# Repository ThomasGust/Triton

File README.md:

# Triton
Code for the Triton Robotics MATE ROV Competition Team

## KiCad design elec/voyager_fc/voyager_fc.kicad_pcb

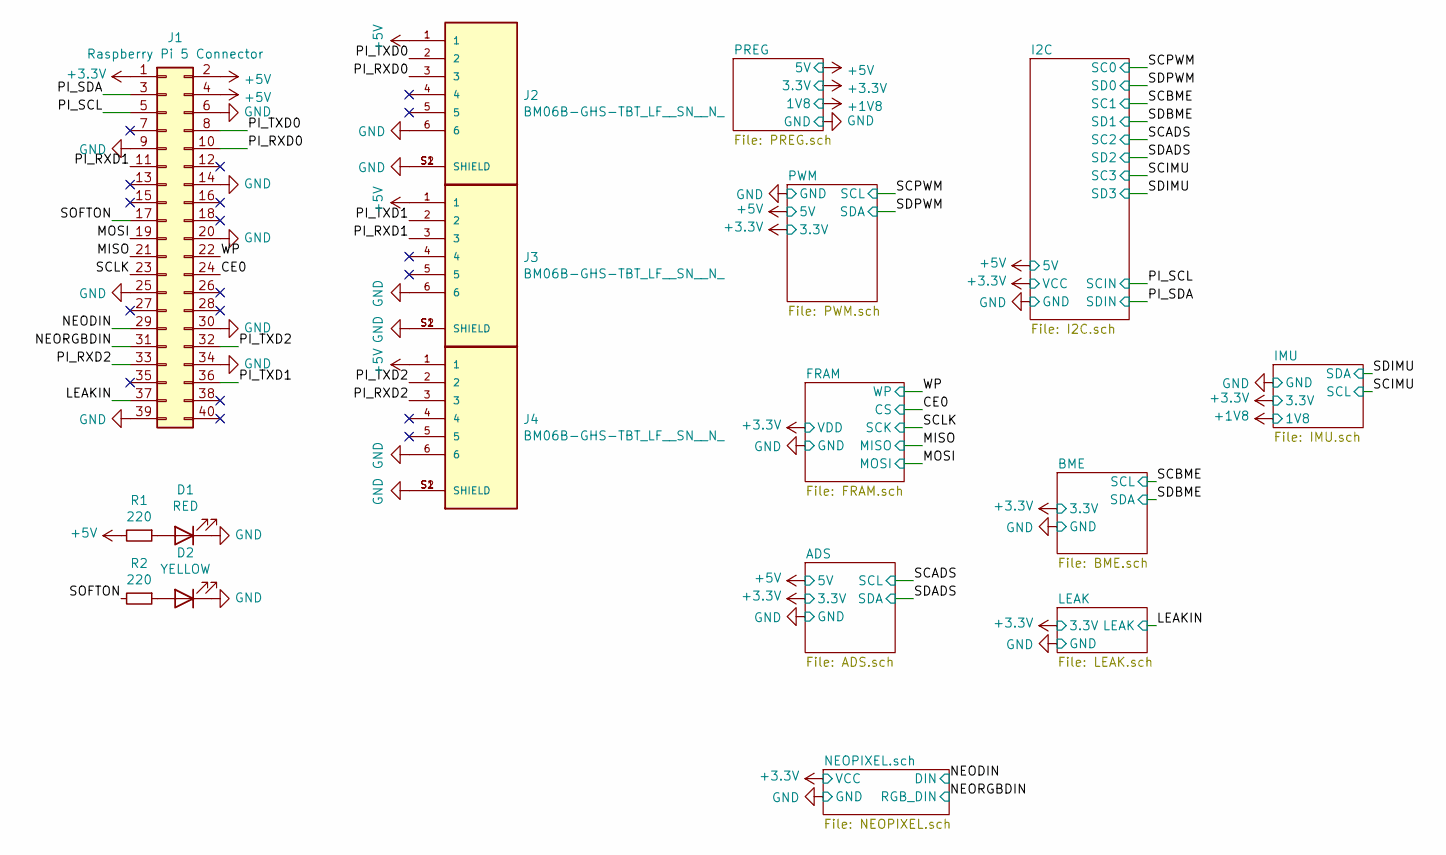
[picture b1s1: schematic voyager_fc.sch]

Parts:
D1: RED; LED_0603_1608Metric
D2: YELLOW; LED_0603_1608Metric
J1: Raspberry Pi 5 Connector; PinSocket_2x20_P2.54mm_Vertical
J2, J3, J4: BM06B-GHS-TBT_LF__SN__N_; JST_BM06B-GHS-TBT_LF__SN__N_; PARTREV N/A
R1, R2: 220; R_0402_1005Metric

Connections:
+3V3: J1.1; also elsewhere on the board
+5V: J1.2, J1.4, J2.1, J3.1, J4.1, R1.2; also elsewhere on the board
/CE0: J1.24; also elsewhere on the board
/LEAKIN: J1.37; also elsewhere on the board
/MISO: J1.21; also elsewhere on the board
/MOSI: J1.19; also elsewhere on the board
/NEODIN: J1.29; also elsewhere on the board
/NEORGBDIN: J1.31; also elsewhere on the board
/PI_RXD0: J1.10, J2.3
/PI_RXD1: J1.11, J3.3
/PI_RXD2: J1.33, J4.3
/PI_SCL: J1.5; also elsewhere on the board
/PI_SDA: J1.3; also elsewhere on the board
/PI_TXD0: J1.8, J2.2
/PI_TXD1: J1.36, J3.2
/PI_TXD2: J1.32, J4.2
/SCLK: J1.23; also elsewhere on the board
/SOFTON: J1.17, R2.2
/WP: J1.22; also elsewhere on the board
GND: D1.1 (K), D2.1 (K), J1.6, J1.9, J1.14, J1.20, J1.25, J1.30, J1.34, J1.39, J2.6, J2.S1 (SHIELD), J2.S2 (SHIELD), J3.6, J3.S1 (SHIELD), J3.S2 (SHIELD), J4.6, J4.S1 (SHIELD), J4.S2 (SHIELD); also elsewhere on the board
unnamed: D1.2 (A), R1.1
unnamed: D2.2 (A), R2.1

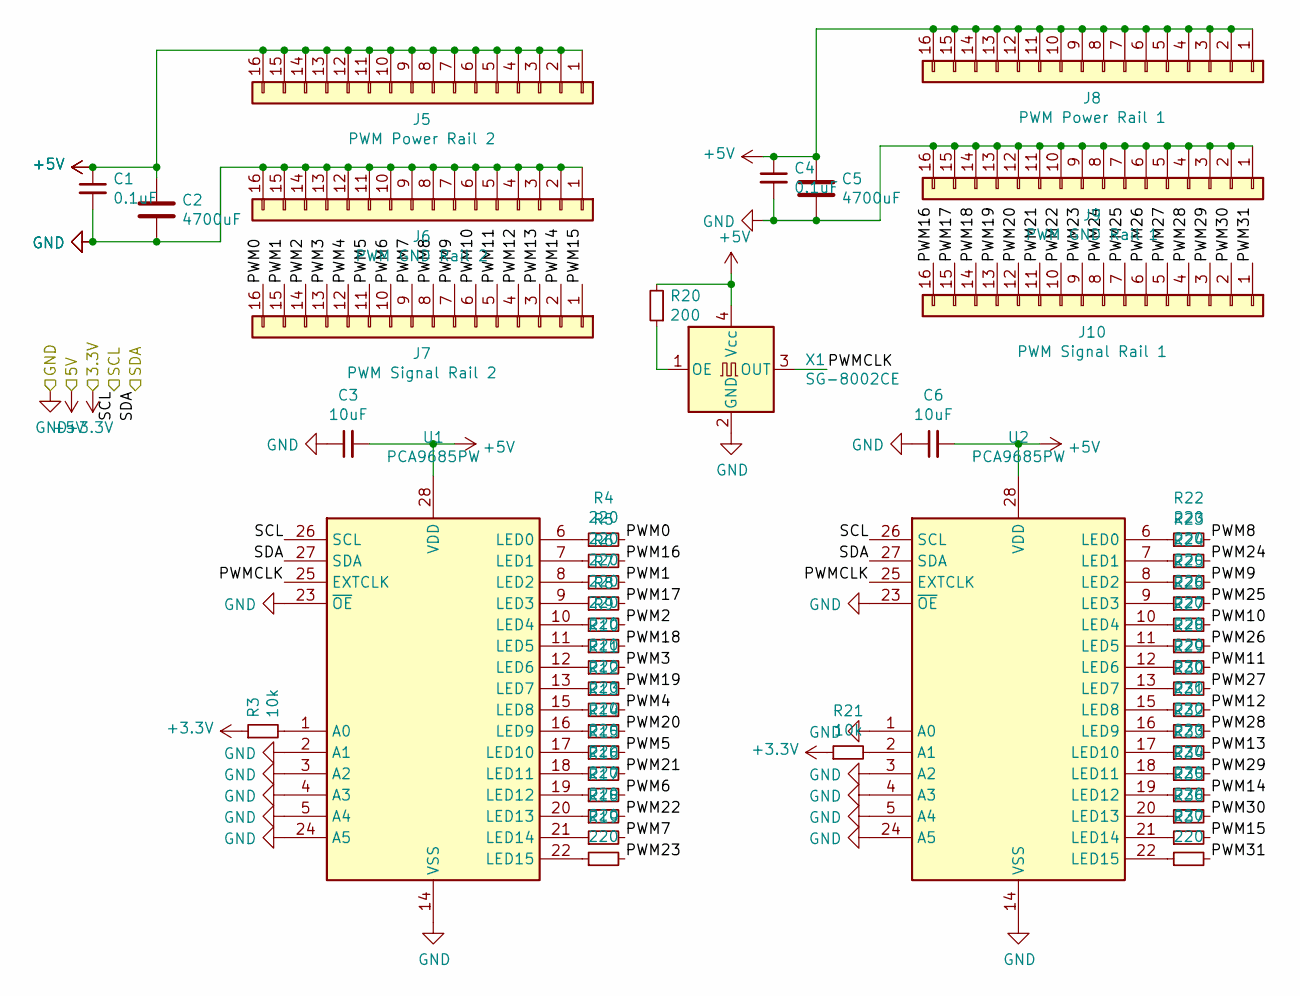
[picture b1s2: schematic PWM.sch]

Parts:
C1, C4: 0.1uF; C_0402_1005Metric
C2, C5: 4700uF; CP_Radial_D10.0mm_P5.00mm
C3, C6: 10uF; C_0603_1608Metric
J5: PWM Power Rail 2; PinHeader_1x16_P2.54mm_Vertical
J6: PWM GND Rail 2; PinHeader_1x16_P2.54mm_Vertical
J7: PWM Signal Rail 2; PinHeader_1x16_P2.54mm_Vertical
J8: PWM Power Rail 1; PinHeader_1x16_P2.54mm_Vertical
J9: PWM GND Rail 1; PinHeader_1x16_P2.54mm_Vertical
J10: PWM Signal Rail 1; PinHeader_1x16_P2.54mm_Vertical
R3, R21: 10k; R_0603_1608Metric
R4, R5, R6, R7, R8, R9, R10, R11, R12, R13, R14, R15, R16, R17, R18, R19, R22, R23, R24, R25, R26, R27, R28, R29, R30, R31, R32, R33, R34, R35, R36, R37: 220; R_0402_1005Metric
R20: 200; R_0402_1005Metric
U1, U2: PCA9685PW; TSSOP-28_4.4x9.7mm_P0.65mm
X1: SG-8002CE; Oscillator_SMD_SeikoEpson_SG8002CE-4Pin_3.2x2.5mm

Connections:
+3V3: R3.1, R21.1; also elsewhere on the board
+5V: C1.1, C2.1, C3.2, C4.1, C5.1, C6.2, J5.1, J5.2, J5.3, J5.4, J5.5, J5.6, J5.7, J5.8, J5.9, J5.10, J5.11, J5.12, J5.13, J5.14, J5.15, J5.16, J8.1, J8.2, J8.3, J8.4, J8.5, J8.6, J8.7, J8.8, J8.9, J8.10, J8.11, J8.12, J8.13, J8.14, J8.15, J8.16, R20.2, U1.28 (VDD), U2.28 (VDD), X1.4 (Vcc); also elsewhere on the board
/PWM/PWM0: J7.16, R4.2
/PWM/PWM1: J7.15, R6.2
/PWM/PWM2: J7.14, R8.2
/PWM/PWM3: J7.13, R10.2
/PWM/PWM4: J7.12, R12.2
/PWM/PWM5: J7.11, R14.2
/PWM/PWM6: J7.10, R16.2
/PWM/PWM7: J7.9, R18.2
/PWM/PWM8: J7.8, R22.2
/PWM/PWM9: J7.7, R24.2
/PWM/PWM10: J7.6, R26.2
/PWM/PWM11: J7.5, R28.2
/PWM/PWM12: J7.4, R30.2
/PWM/PWM13: J7.3, R32.2
/PWM/PWM14: J7.2, R34.2
/PWM/PWM15: J7.1, R36.2
/PWM/PWM16: J10.16, R5.2
/PWM/PWM17: J10.15, R7.2
/PWM/PWM18: J10.14, R9.2
/PWM/PWM19: J10.13, R11.2
/PWM/PWM20: J10.12, R13.2
/PWM/PWM21: J10.11, R15.2
/PWM/PWM22: J10.10, R17.2
/PWM/PWM23: J10.9, R19.2
/PWM/PWM24: J10.8, R23.2
/PWM/PWM25: J10.7, R25.2
/PWM/PWM26: J10.6, R27.2
/PWM/PWM27: J10.5, R29.2
/PWM/PWM28: J10.4, R31.2
/PWM/PWM29: J10.3, R33.2
/PWM/PWM30: J10.2, R35.2
/PWM/PWM31: J10.1, R37.2
/PWM/PWMCLK: U1.25 (EXTCLK), U2.25 (EXTCLK), X1.3 (OUT)
/SCPWM: U1.26 (SCL), U2.26 (SCL); also elsewhere on the board
/SDPWM: U1.27 (SDA), U2.27 (SDA); also elsewhere on the board
GND: C1.2, C2.2, C3.1, C4.2, C5.2, C6.1, J6.1, J6.2, J6.3, J6.4, J6.5, J6.6, J6.7, J6.8, J6.9, J6.10, J6.11, J6.12, J6.13, J6.14, J6.15, J6.16, J9.1, J9.2, J9.3, J9.4, J9.5, J9.6, J9.7, J9.8, J9.9, J9.10, J9.11, J9.12, J9.13, J9.14, J9.15, J9.16, U1.2 (A1), U1.3 (A2), U1.4 (A3), U1.5 (A4), U1.14 (VSS), U1.23 (~OE), U1.24 (A5), U2.1 (A0), U2.3 (A2), U2.4 (A3), U2.5 (A4), U2.14 (VSS), U2.23 (~OE), U2.24 (A5), X1.2 (GND); also elsewhere on the board
unnamed: R3.2, U1.1 (A0)
unnamed: R4.1, U1.6 (LED0)
unnamed: R5.1, U1.7 (LED1)
unnamed: R6.1, U1.8 (LED2)
unnamed: R7.1, U1.9 (LED3)
unnamed: R8.1, U1.10 (LED4)
unnamed: R9.1, U1.11 (LED5)
unnamed: R10.1, U1.12 (LED6)
unnamed: R11.1, U1.13 (LED7)
unnamed: R12.1, U1.15 (LED8)
unnamed: R13.1, U1.16 (LED9)
unnamed: R14.1, U1.17 (LED10)
unnamed: R15.1, U1.18 (LED11)
unnamed: R16.1, U1.19 (LED12)
unnamed: R17.1, U1.20 (LED13)
unnamed: R18.1, U1.21 (LED14)
unnamed: R19.1, U1.22 (LED15)
unnamed: R20.1, X1.1 (OE)
unnamed: R21.2, U2.2 (A1)
unnamed: R22.1, U2.6 (LED0)
unnamed: R23.1, U2.7 (LED1)
unnamed: R24.1, U2.8 (LED2)
unnamed: R25.1, U2.9 (LED3)
unnamed: R26.1, U2.10 (LED4)
unnamed: R27.1, U2.11 (LED5)
unnamed: R28.1, U2.12 (LED6)
unnamed: R29.1, U2.13 (LED7)
unnamed: R30.1, U2.15 (LED8)
unnamed: R31.1, U2.16 (LED9)
unnamed: R32.1, U2.17 (LED10)
unnamed: R33.1, U2.18 (LED11)
unnamed: R34.1, U2.19 (LED12)
unnamed: R35.1, U2.20 (LED13)
unnamed: R36.1, U2.21 (LED14)
unnamed: R37.1, U2.22 (LED15)

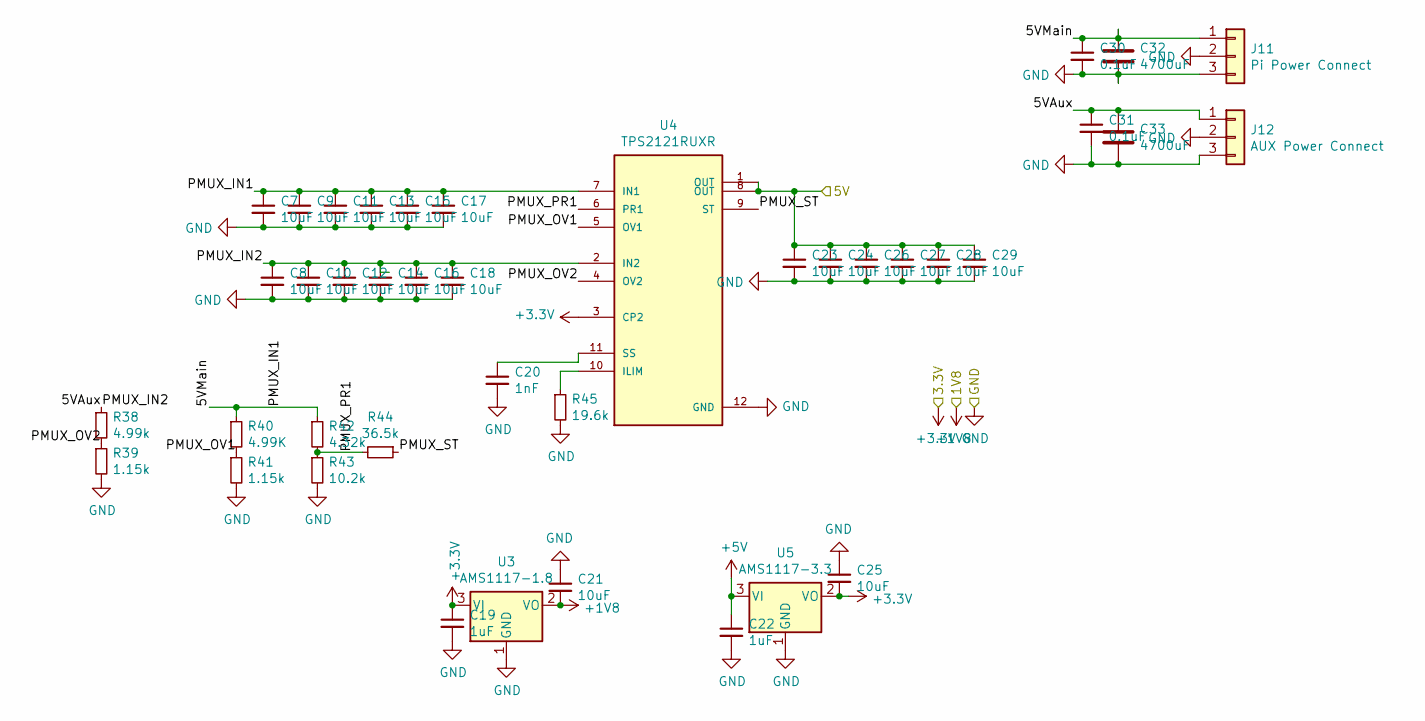
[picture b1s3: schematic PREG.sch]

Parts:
C7, C8, C9, C10, C11, C12, C13, C14, C15, C16, C17, C18, C21, C23, C24, C25, C26, C27, C28, C29: 10uF; C_0603_1608Metric
C19, C22: 1uF; C_0402_1005Metric
C20: 1nF; C_0402_1005Metric
C30, C31: 0.1uF; C_0402_1005Metric
C32, C33: 4700uF; CP_Radial_D10.0mm_P5.00mm
J11: Pi Power Connect; PinHeader_1x03_P2.54mm_Vertical
J12: AUX Power Connect; PinHeader_1x03_P2.54mm_Vertical
R38: 4.99k; R_0603_1608Metric
R39, R41: 1.15k; R_0603_1608Metric
R40: 4.99K; R_0603_1608Metric
R42: 4.32k; R_0603_1608Metric
R43: 10.2k; R_0603_1608Metric
R44: 36.5k; R_0603_1608Metric
R45: 19.6k; R_0603_1608Metric
U3: AMS1117-1.8; SOT-223-3_TabPin2
U4: TPS2121RUXR; IC_TPS2121RUXR
U5: AMS1117-3.3; SOT-223-3_TabPin2

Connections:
+1V8: C21.2, U3.2 (VO); also elsewhere on the board
+3V3: C19.1, C25.2, U3.3 (VI), U4.3 (CP2), U5.2 (VO); also elsewhere on the board
+5V: C22.1, C23.1, C24.1, C26.1, C27.1, C28.1, C29.1, U4.1 (OUT), U4.8 (OUT), U5.3 (VI); also elsewhere on the board
/PREG/5VAux: C8.1, C10.1, C12.1, C14.1, C16.1, C18.1, C31.1, C33.1, J12.1, R38.1, U4.2 (IN2)
/PREG/5VMain: C7.1, C9.1, C11.1, C13.1, C15.1, C17.1, C30.1, C32.1, J11.1, R40.1, R42.1, U4.7 (IN1)
/PREG/PMUX_OV1: R40.2, R41.1, U4.5 (OV1)
/PREG/PMUX_OV2: R38.2, R39.1, U4.4 (OV2)
/PREG/PMUX_PR1: R42.2, R43.1, R44.2, U4.6 (PR1)
/PREG/PMUX_ST: R44.1, U4.9 (ST)
GND: C7.2, C8.2, C9.2, C10.2, C11.2, C12.2, C13.2, C14.2, C15.2, C16.2, C17.2, C18.2, C19.2, C20.2, C21.1, C22.2, C23.2, C24.2, C25.1, C26.2, C27.2, C28.2, C29.2, C30.2, C31.2, C32.2, C33.2, J11.2, J11.3, J12.2, J12.3, R39.2, R41.2, R43.2, R45.2, U3.1 (GND), U4.12 (GND), U5.1 (GND); also elsewhere on the board
unnamed: C20.1, U4.11 (SS)
unnamed: R45.1, U4.10 (ILIM)

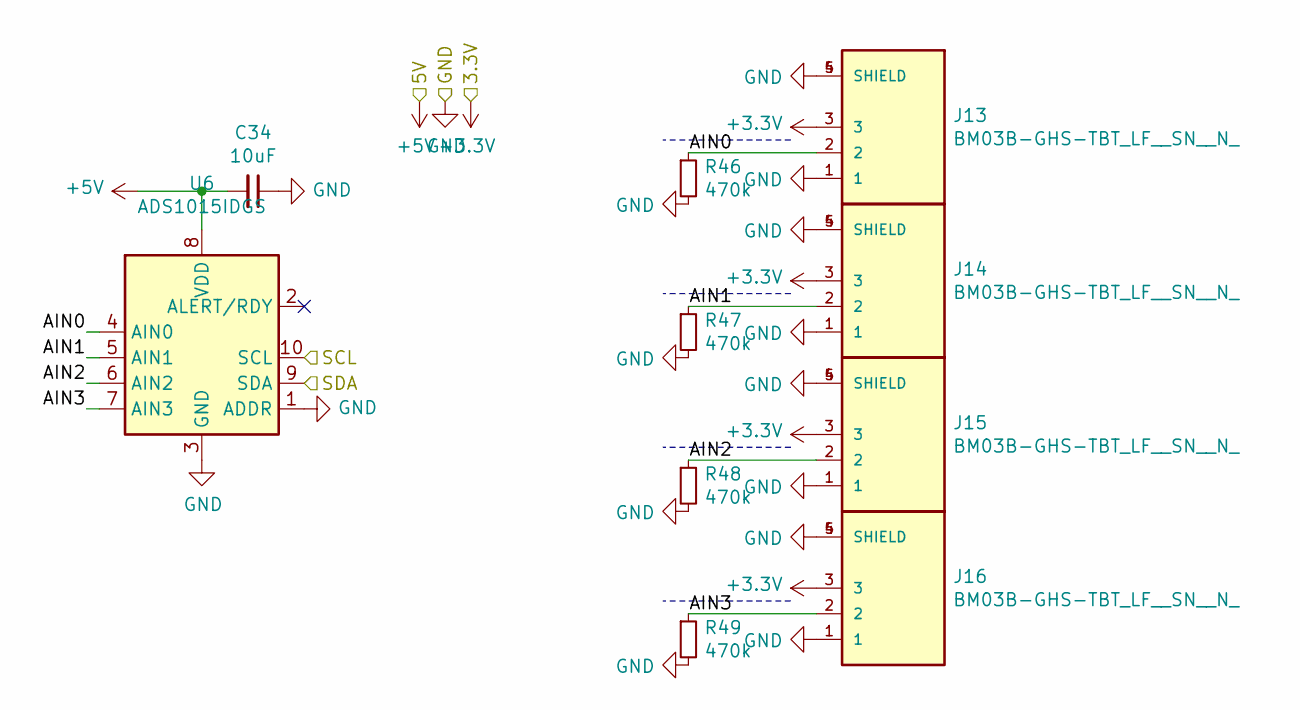
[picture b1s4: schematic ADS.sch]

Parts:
C34: 10uF; C_0603_1608Metric
J13, J14, J15, J16: BM03B-GHS-TBT_LF__SN__N_; CONN_BM03B-GHS-TBT_LF__SN__N_
R46, R47, R48, R49: 470k; R_0603_1608Metric
U6: ADS1015IDGS; TSSOP-10_3x3mm_P0.5mm

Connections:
+3V3: J13.3, J14.3, J15.3, J16.3; also elsewhere on the board
+5V: C34.2, U6.8 (VDD); also elsewhere on the board
/ADS/AIN0: J13.2, R46.1, U6.4 (AIN0)
/ADS/AIN1: J14.2, R47.1, U6.5 (AIN1)
/ADS/AIN2: J15.2, R48.1, U6.6 (AIN2)
/ADS/AIN3: J16.2, R49.1, U6.7 (AIN3)
/SCADS: U6.10 (SCL); also elsewhere on the board
/SDADS: U6.9 (SDA); also elsewhere on the board
GND: C34.1, J13.1, J13.4 (SHIELD), J13.5 (SHIELD), J14.1, J14.4 (SHIELD), J14.5 (SHIELD), J15.1, J15.4 (SHIELD), J15.5 (SHIELD), J16.1, J16.4 (SHIELD), J16.5 (SHIELD), R46.2, R47.2, R48.2, R49.2, U6.1 (ADDR), U6.3 (GND); also elsewhere on the board

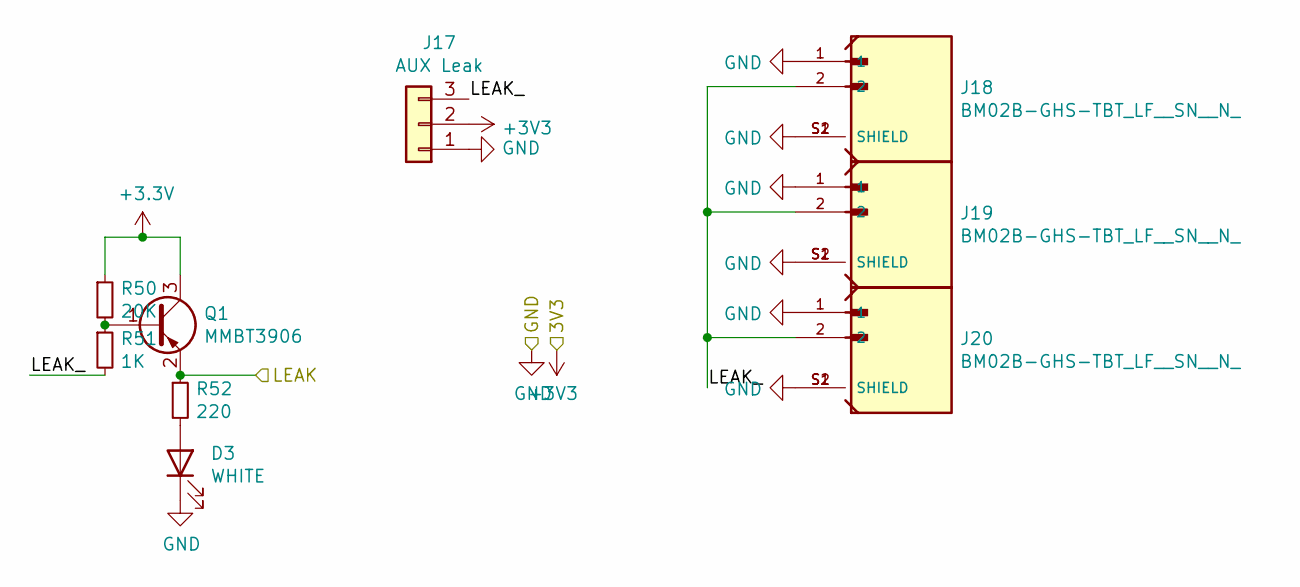
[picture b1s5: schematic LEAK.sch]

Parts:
D3: WHITE; LED_0603_1608Metric
J17: AUX Leak; PinHeader_1x03_P2.54mm_Vertical
J18, J19, J20: BM02B-GHS-TBT_LF__SN__N_; JST_BM02B-GHS-TBT_LF__SN__N_
Q1: MMBT3906; SOT-23
R50: 20K; R_0603_1608Metric
R51: 1K; R_0603_1608Metric
R52: 220; R_0402_1005Metric

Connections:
+3V3: J17.2, Q1.3 (C), R50.1; also elsewhere on the board
/LEAK/LEAK_: J17.3, J18.2, J19.2, J20.2, R51.2
/LEAKIN: Q1.2 (E), R52.1; also elsewhere on the board
GND: D3.1 (K), J17.1, J18.1, J18.S1 (SHIELD), J18.S2 (SHIELD), J19.1, J19.S1 (SHIELD), J19.S2 (SHIELD), J20.1, J20.S1 (SHIELD), J20.S2 (SHIELD); also elsewhere on the board
unnamed: D3.2 (A), R52.2
unnamed: Q1.1 (B), R50.2, R51.1

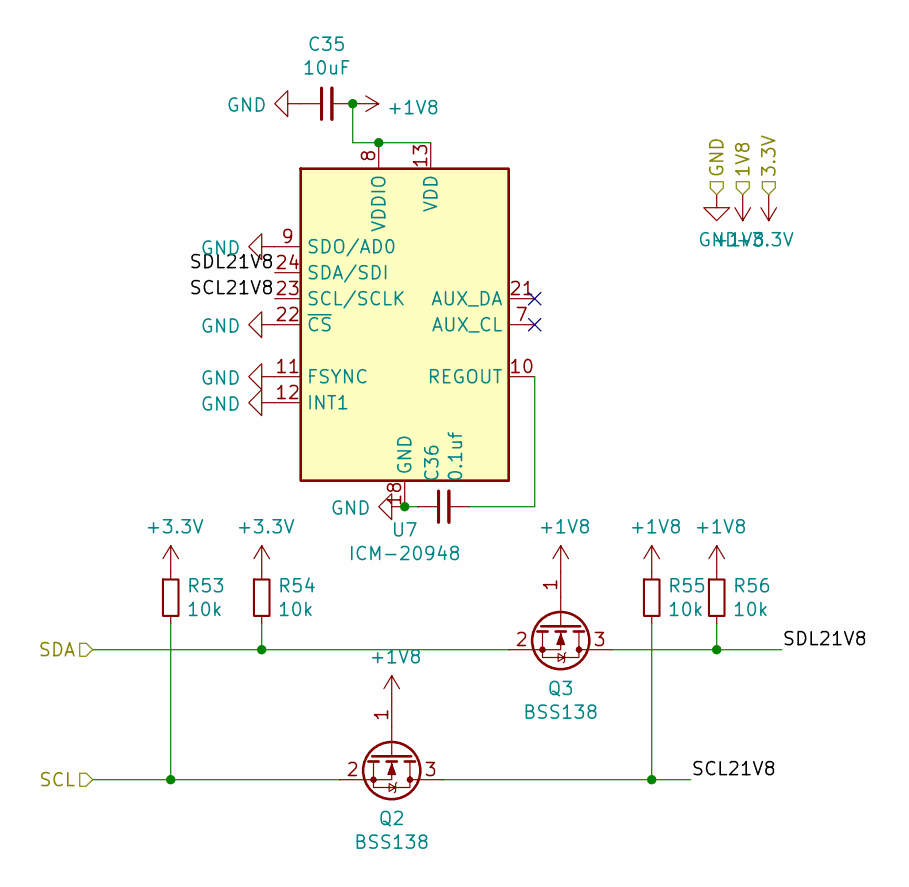
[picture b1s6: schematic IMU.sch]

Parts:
C35: 10uF; C_0603_1608Metric
C36: 0.1uf; C_0402_1005Metric
Q2, Q3: BSS138; SOT-23
R53, R54, R55, R56: 10k; R_0603_1608Metric
U7: ICM-20948; InvenSense_QFN-24_3x3mm_P0.4mm

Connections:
+1V8: C35.2, Q2.1 (G), Q3.1 (G), R55.1, R56.1, U7.8 (VDDIO), U7.13 (VDD); also elsewhere on the board
+3V3: R53.1, R54.1; also elsewhere on the board
/IMU/SCL21V8: Q2.3 (D), R55.2, U7.23 (SCL/SCLK)
/IMU/SDL21V8: Q3.3 (D), R56.2, U7.24 (SDA/SDI)
/SCIMU: Q2.2 (S), R53.2; also elsewhere on the board
/SDIMU: Q3.2 (S), R54.2; also elsewhere on the board
GND: C35.1, C36.1, U7.9 (SDO/AD0), U7.11 (FSYNC), U7.12 (INT1), U7.18 (GND), U7.20 (GND), U7.22 (~CS); also elsewhere on the board
unnamed: C36.2, U7.10 (REGOUT)

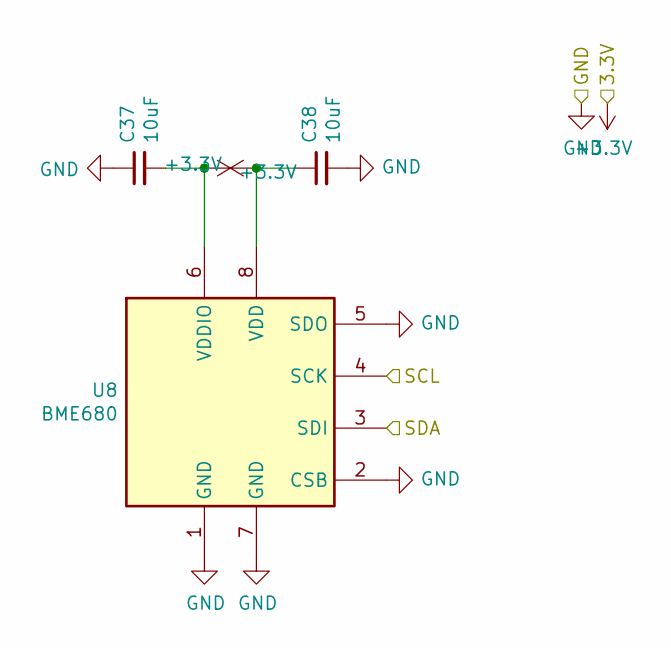
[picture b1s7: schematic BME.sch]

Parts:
C37, C38: 10uF; C_0603_1608Metric
U8: BME680; Bosch_LGA-8_3x3mm_P0.8mm_ClockwisePinNumbering

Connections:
+3V3: C37.2, C38.1, U8.6 (VDDIO), U8.8 (VDD); also elsewhere on the board
/SCBME: U8.4 (SCK); also elsewhere on the board
/SDBME: U8.3 (SDI); also elsewhere on the board
GND: C37.1, C38.2, U8.1 (GND), U8.2 (CSB), U8.5 (SDO), U8.7 (GND); also elsewhere on the board

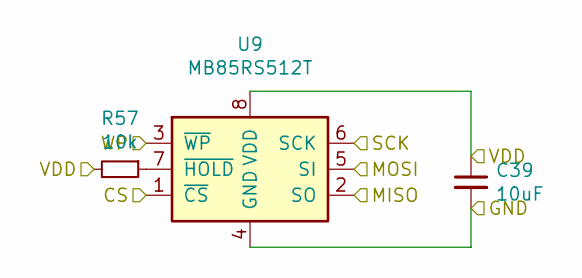
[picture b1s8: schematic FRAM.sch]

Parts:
C39: 10uF; C_0603_1608Metric
R57: 10k; R_0603_1608Metric
U9: MB85RS512T; SOIC127P600X88-8N

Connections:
+3V3: C39.1, R57.2, U9.8 (VDD); also elsewhere on the board
/CE0: U9.1 (~CS); also elsewhere on the board
/MISO: U9.2 (SO); also elsewhere on the board
/MOSI: U9.5 (SI); also elsewhere on the board
/SCLK: U9.6 (SCK); also elsewhere on the board
/WP: U9.3 (~WP); also elsewhere on the board
GND: C39.2, U9.4 (GND); also elsewhere on the board
unnamed: R57.1, U9.7 (~HOLD)

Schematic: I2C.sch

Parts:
C40, C41, C42, C43, C44, C45, C46, C47, C48, C53, C54, C55, C56: 10uF; C_0603_1608Metric
C49, C50, C51, C52: 0.1uF; C_0402_1005Metric
J21, J22, J23, J24: BM04B-GHS-TBT_LF__SN__N_; JST_BM04B-GHS-TBT_LF__SN__N_; PARTREV N/A
R58, R59, R60, R61, R62, R63, R64, R65, R66, R67, R68, R69, R70, R71, R72, R73, R74: 10k; R_0603_1608Metric
U10: TCA9548APWR; TSSOP-24_4.4x7.8mm_P0.65mm
U11, U12, U13, U14: LTC4311CDC_TRMPBF; DFN-6_DC; MANUFACTURER_PART_NUMBER ltc4311cdc#trpbf
U15, U16, U17, U18: TXS0102YZP; Texas_DSBGA-8_0.9x1.9mm_Layout2x4_P0.5mm

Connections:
+3V3: C44.1, C45.1, C46.1, C47.1, C48.1, C49.1, C50.1, C51.1, C52.1, C53.1, C54.1, C55.1, C56.1, R58.2, R59.2, R60.2, R61.2, R62.2, R63.1, R64.2, R65.1, R66.2, R67.1, R68.2, R69.1, R70.2, R71.2, R72.2, R73.2, R74.2, U10.24 (VCC), U11.3 (VCC), U12.3 (VCC), U13.3 (VCC), U14.3 (VCC), U15.B2 (VCCB), U15.C1 (VCCA), U16.B2 (VCCB), U16.C1 (VCCA), U17.B2 (VCCB), U17.C1 (VCCA), U18.B2 (VCCB), U18.C1 (VCCA); also elsewhere on the board
+5V: C40.1, C41.1, C42.1, C43.1, J21.1, J22.1, J23.1, J24.1; also elsewhere on the board
/I2C/OSC4: J21.2, U15.A1 (B2)
/I2C/OSC5: J22.2, U16.A1 (B2)
/I2C/OSC6: J23.2, U17.A1 (B2)
/I2C/OSC7: J24.2, U18.A1 (B2)
/I2C/OSD4: J21.3, U15.A2 (B1)
/I2C/OSD5: J22.3, U16.A2 (B1)
/I2C/OSD6: J23.3, U17.A2 (B1)
/I2C/OSD7: J24.3, U18.A2 (B1)
/I2C/SC4: R63.2, U10.14 (SC4), U11.5 (BUS2), U15.D1 (A2)
/I2C/SC5: R65.2, U10.16 (SC5), U12.5 (BUS2), U16.D1 (A2)
/I2C/SC6: R67.2, U10.18 (SC6), U13.5 (BUS2), U17.D1 (A2)
/I2C/SC7: R69.2, U10.20 (SC7), U14.5 (BUS2), U18.D1 (A2)
/I2C/SD4: R64.1, U10.13 (SD4), U11.4 (BUS1), U15.D2 (A1)
/I2C/SD5: R66.1, U10.15 (SD5), U12.4 (BUS1), U16.D2 (A1)
/I2C/SD6: R68.1, U10.17 (SD6), U13.4 (BUS1), U17.D2 (A1)
/I2C/SD7: R70.1, U10.19 (SD7), U14.4 (BUS1), U18.D2 (A1)
/PI_SCL: U10.22 (SCL); also elsewhere on the board
/PI_SDA: U10.23 (SDA); also elsewhere on the board
/SCADS: U10.9 (SC2); also elsewhere on the board
/SCBME: U10.7 (SC1); also elsewhere on the board
/SCIMU: U10.11 (SC3); also elsewhere on the board
/SCPWM: U10.5 (SC0); also elsewhere on the board
/SDADS: U10.8 (SD2); also elsewhere on the board
/SDBME: U10.6 (SD1); also elsewhere on the board
/SDIMU: U10.10 (SD3); also elsewhere on the board
/SDPWM: U10.4 (SD0); also elsewhere on the board
GND: C40.2, C41.2, C42.2, C43.2, C44.2, C45.2, C46.2, C47.2, C48.2, C49.2, C50.2, C51.2, C52.2, C53.2, C54.2, C55.2, C56.2, J21.4, J21.S1 (SHIELD), J21.S2 (SHIELD), J22.4, J22.S1 (SHIELD), J22.S2 (SHIELD), J23.4, J23.S1 (SHIELD), J23.S2 (SHIELD), J24.4, J24.S1 (SHIELD), J24.S2 (SHIELD), U10.1 (A0), U10.2 (A1), U10.12 (GND), U10.21 (A2), U11.6 (GND), U11.7 (EPAD), U12.6 (GND), U12.7 (EPAD), U13.6 (GND), U13.7 (EPAD), U14.6 (GND), U14.7 (EPAD), U15.B1 (GND), U16.B1 (GND), U17.B1 (GND), U18.B1 (GND); also elsewhere on the board
unnamed: R58.1, U10.3 (~RESET)
unnamed: R59.1, U11.1 (ENABLE)
unnamed: R60.1, U12.1 (ENABLE)
unnamed: R61.1, U13.1 (ENABLE)
unnamed: R62.1, U14.1 (ENABLE)
unnamed: R71.1, U15.C2 (OE)
unnamed: R72.1, U16.C2 (OE)
unnamed: R73.1, U17.C2 (OE)
unnamed: R74.1, U18.C2 (OE)

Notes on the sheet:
I2C module integrates multiplexing with logic level shifting and active termination/range extension.
TCA9548 I2C MUX gives an 1:8 configuration on the raspberry pi's primary i2c bus.
Four of these new busses are auto level shifted with a TXS0102 and actively terminated with an LTC4311
for off board communication, and the other are used for communication within the hat.

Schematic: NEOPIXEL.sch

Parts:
C57: 100nF; C_0402_1005Metric
D4: SK6812; LED_SK6812_PLCC4_5.0x5.0mm_P3.2mm
R75: 470; R_0603_1608Metric
R76: 470; R_0402_1005Metric
U19: SN74LV1T34DBV; SOT-23-5

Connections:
+3V3: C57.1, D4.3 (VDD), U19.5 (VCC); also elsewhere on the board
/NEODIN: U19.2 (A); also elsewhere on the board
/NEORGBDIN: R75.2; also elsewhere on the board
GND: C57.2, D4.1 (VSS), U19.3 (GND); also elsewhere on the board
unnamed: D4.2 (DIN), R76.1
unnamed: R75.1, R76.2, U19.4 (Y)

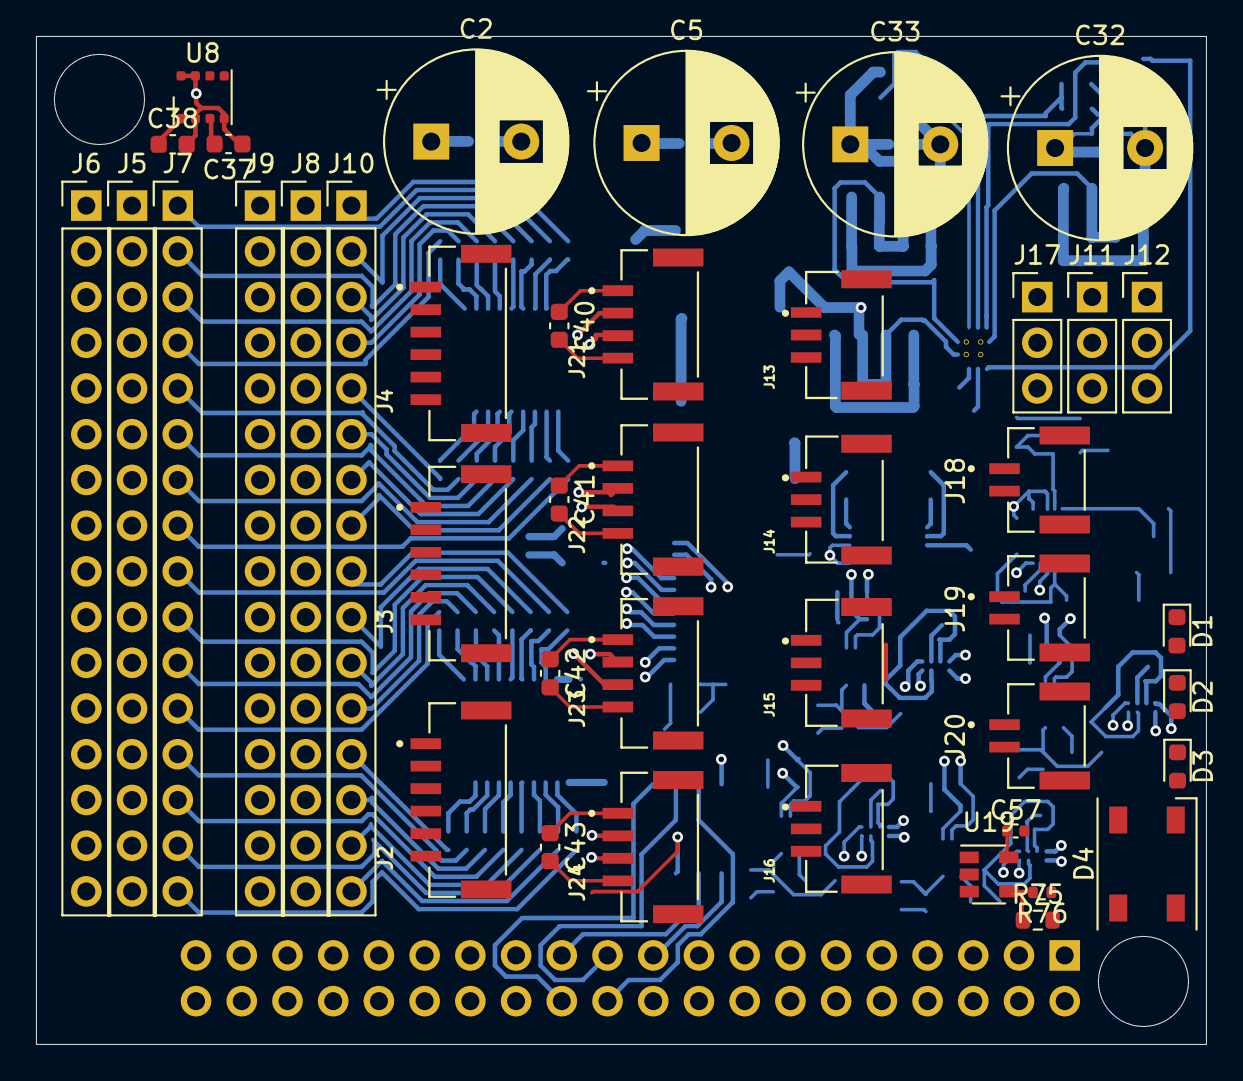
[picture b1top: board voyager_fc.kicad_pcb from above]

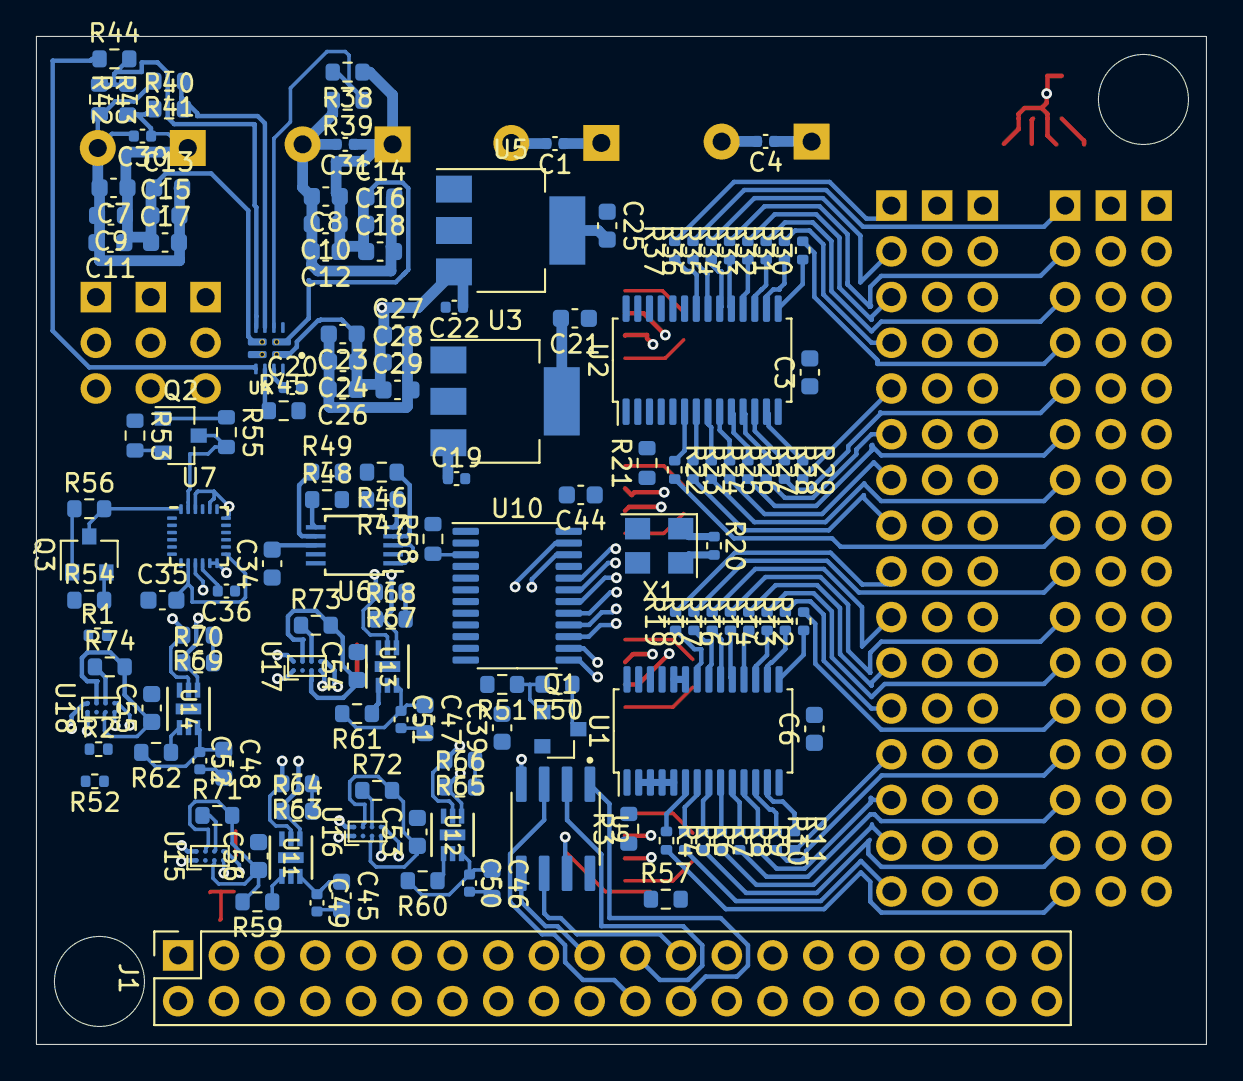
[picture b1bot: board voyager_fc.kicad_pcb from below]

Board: 6 copper layers, 65.0 x 56.0 mm, 184 parts (142 on the bottom side), 145 nets.

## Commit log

2024-09-15 Add project files so far
2024-10-23 Start pubsub updates
2024-10-31 Add kicad files for voyager FC draft
2024-10-31 Update voyager annotations
2024-10-31 Create bill of materials for voyager fc
2024-10-31 Start schematic makeover with proper hierarchy
2024-11-01 Move connectors inside schematics
2024-11-02 Place all components and start route

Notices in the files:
parts and their libraries:
Copyright C 2016 Accelerated Designs. All rights reserved
